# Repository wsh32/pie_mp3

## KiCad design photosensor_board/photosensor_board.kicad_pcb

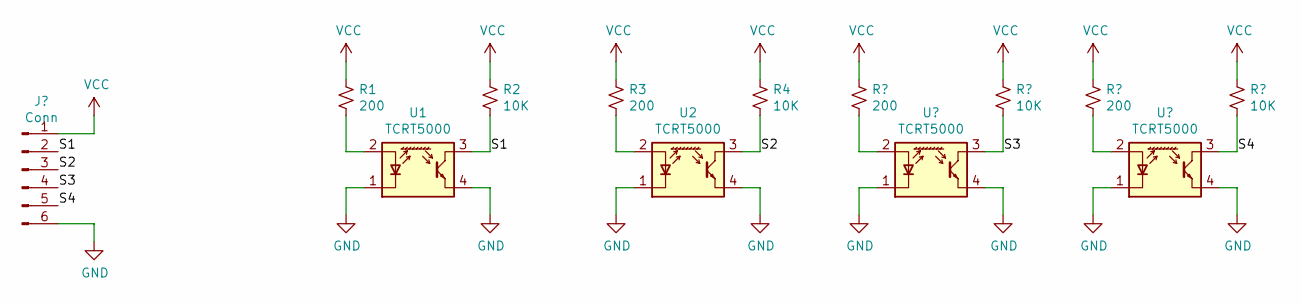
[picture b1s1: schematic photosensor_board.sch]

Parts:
R1, R3: 200; R_0805_2012Metric_Pad1.20x1.40mm_HandSolder
R2, R4: 10K; R_0805_2012Metric_Pad1.20x1.40mm_HandSolder
U1, U2: TCRT5000

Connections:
/S1: R2.2, U1.3 (C); also elsewhere on the board
/S2: R4.2, U2.3 (C); also elsewhere on the board
GND: U1.1 (K), U1.4 (E), U2.1 (K), U2.4 (E); also elsewhere on the board
unnamed: R1.2, U1.2 (A)
unnamed: R3.2, U2.2 (A)
VCC: R1.1, R2.1, R3.1, R4.1; also elsewhere on the board

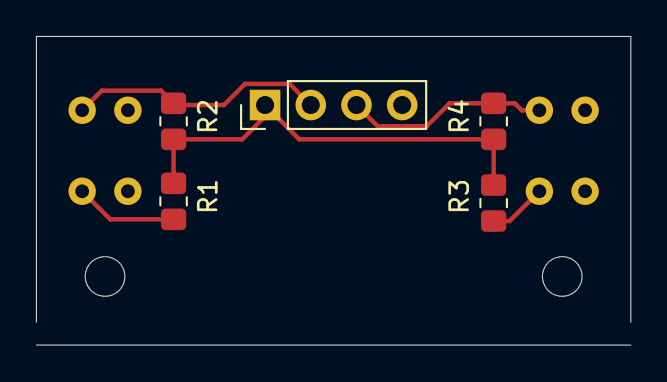
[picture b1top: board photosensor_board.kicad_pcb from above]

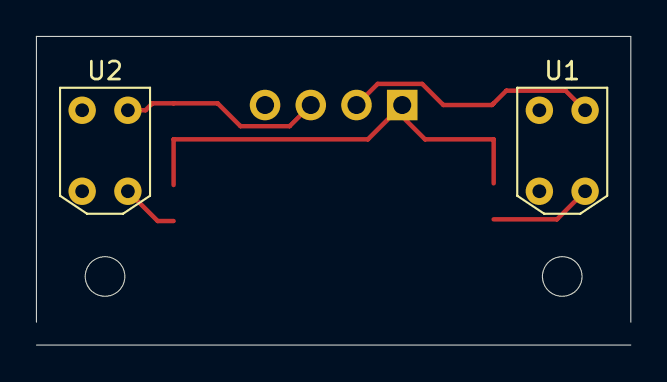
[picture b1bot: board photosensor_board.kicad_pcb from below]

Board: 2 copper layers, 33.0 x 17.1 mm, 7 parts (2 on the bottom side), 6 nets.

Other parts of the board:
J1: Conn; PinHeader_1x04_P2.54mm_Vertical

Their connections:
/S1: J1.2; also elsewhere on the board
/S2: J1.3; also elsewhere on the board
GND: J1.4; also elsewhere on the board
VCC: J1.1; also elsewhere on the board

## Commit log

2021-10-18 mp3 commit
2021-10-21 update code
